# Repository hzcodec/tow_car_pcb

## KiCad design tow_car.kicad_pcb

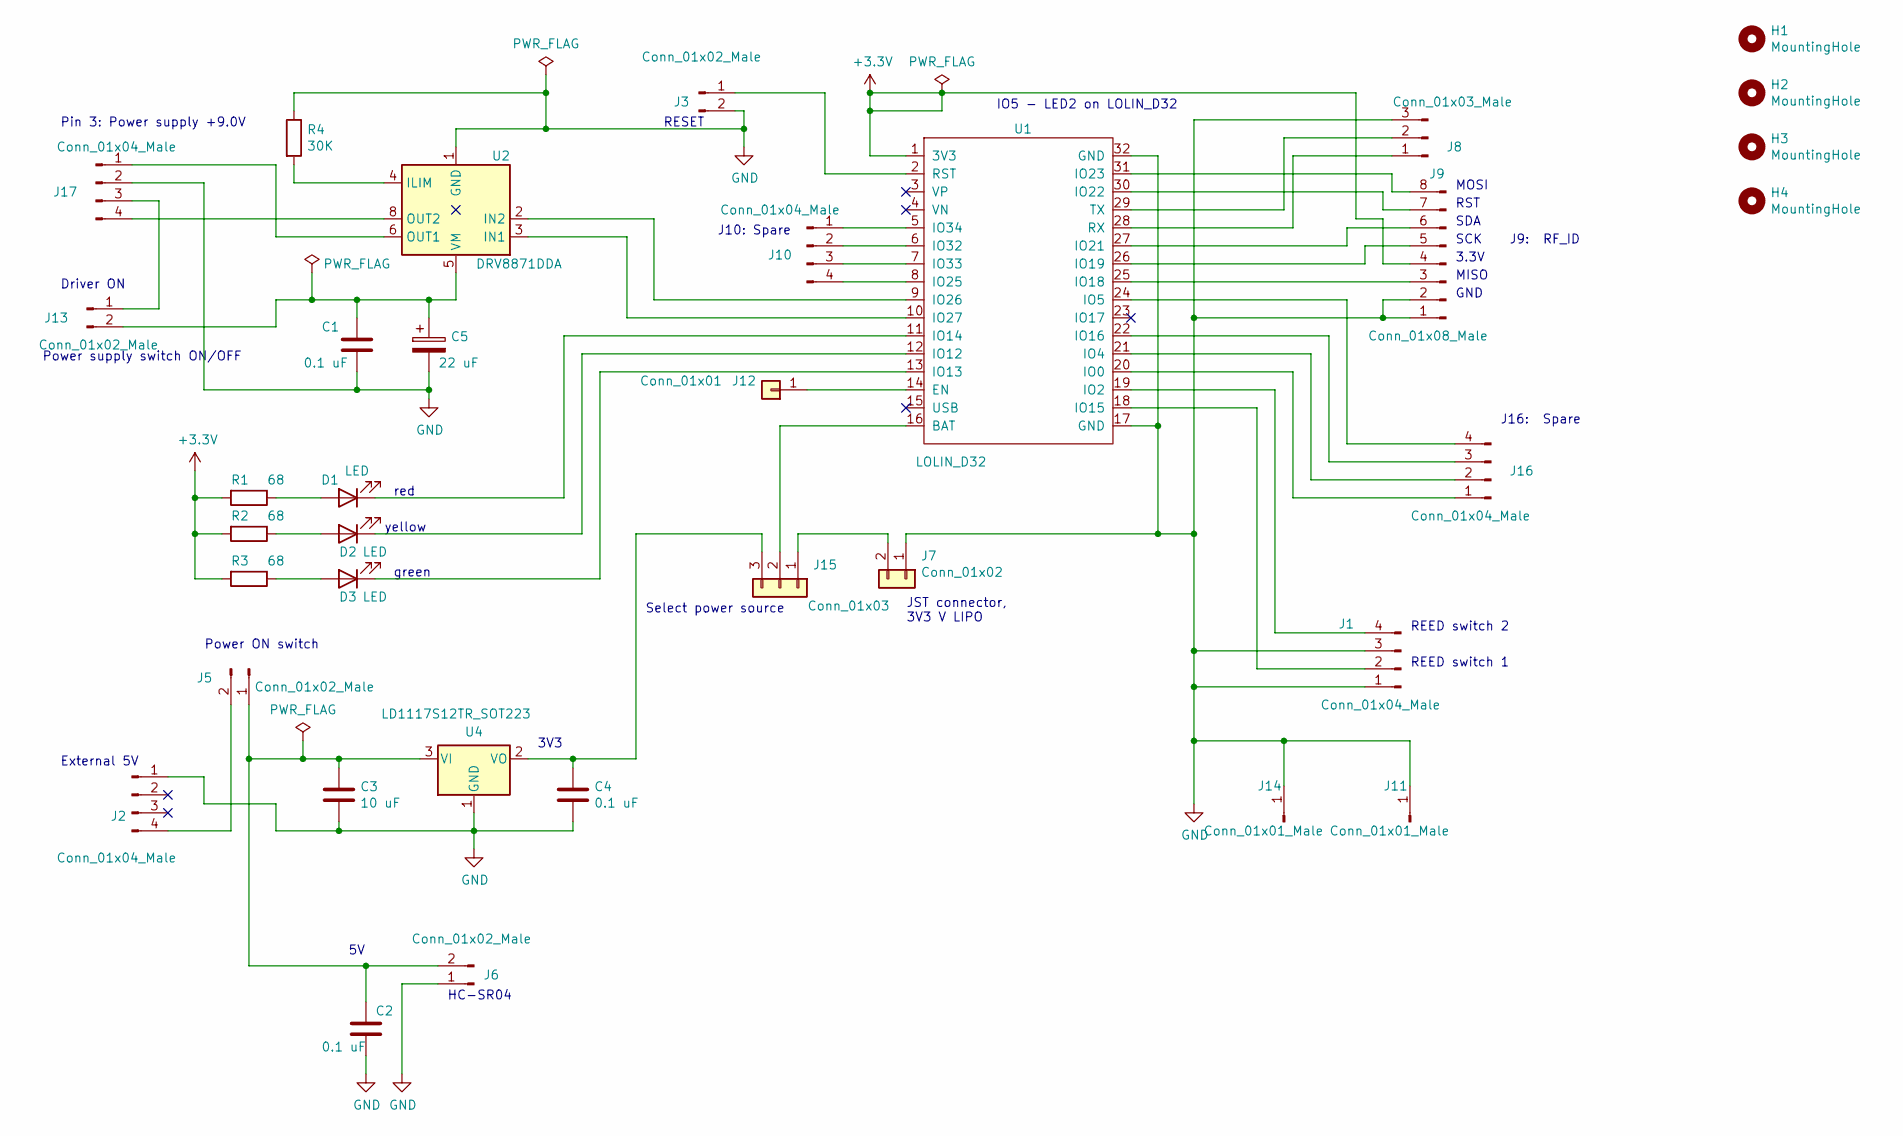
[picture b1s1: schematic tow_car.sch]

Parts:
C1, C2, C4: 0.1 uF; C_1206_3216Metric
C3: 10 uF; C_1206_3216Metric
C5: 22 uF; CP_Elec_3x5.3
D1, D2, D3: LED; LED_1206_3216Metric
H1, H2, H3, H4: MountingHole; MountingHole_3.2mm_M3
J1, J10, J16, J17: Conn_01x04_Male; Molex_Micro-Fit_3.0_43045-0412_2x02_P3.00mm_Vertical
J2: Conn_01x04_Male; USB_A_Molex_105057_Vertical
J3, J5, J6, J13: Conn_01x02_Male; PinHeader_1x02_P2.54mm_Vertical
J7: Conn_01x02; JST_PH_B2B-PH-K_1x02_P2.00mm_Vertical
J8: Conn_01x03_Male; PinHeader_1x03_P2.54mm_Vertical
J9: Conn_01x08_Male; Molex_Micro-Fit_3.0_43045-0800_2x04_P3.00mm_Horizontal
J11, J14: Conn_01x01_Male; PinHeader_1x01_P2.54mm_Vertical
J12: Conn_01x01; PinHeader_1x01_P2.54mm_Vertical
J15: Conn_01x03; PinHeader_1x03_P2.54mm_Vertical
R1, R2, R3: 68; R_1206_3216Metric
R4: 30K; R_1206_3216Metric
U1: LOLIN_D32; DIP32_W22.86
U2: DRV8871DDA; Texas_HTSOP-8-1EP_3.9x4.9mm_P1.27mm_EP2.95x4.9mm_Mask2.4x3.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
U4: LD1117S12TR_SOT223; SOT-223

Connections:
+3V3: J9.4, R1.2, R2.2, R3.2, U1.1 (3V3)
GND: C1.2, C2.2, C3.2, C4.2, C5.2, J1.1, J1.3, J2.1, J3.2, J6.1, J7.1, J8.3, J9.1, J9.2, J11.1, J14.1, J17.2, R4.1, U1.17 (GND), U1.32 (GND), U2.1 (GND), U2.7 (GND), U2.9 (GND), U4.1 (GND); also elsewhere on the board
unnamed: C1.1, C5.1, J13.2, U2.5 (VM)
unnamed: C2.1, C3.1, J5.1, J6.2, U4.3 (VI)
unnamed: C4.1, J15.3, U4.2 (VO)
unnamed: D1.1 (K), U1.11 (IO14)
unnamed: D1.2 (A), R1.1
unnamed: D2.1 (K), U1.12 (IO12)
unnamed: D2.2 (A), R2.1
unnamed: D3.1 (K), U1.13 (IO13)
unnamed: D3.2 (A), R3.1
unnamed: J1.2, U1.18 (IO15)
unnamed: J1.4, U1.19 (IO2)
unnamed: J2.4, J5.2
unnamed: J3.1, U1.2 (RST)
unnamed: J8.1, U1.28 (RX)
unnamed: J8.2, U1.29 (TX)
unnamed: J9.3, U1.25 (IO18)
unnamed: J9.5, U1.26 (IO19)
unnamed: J9.6, U1.27 (IO21)
unnamed: J9.7, U1.30 (IO22)
unnamed: J9.8, U1.31 (IO23)
unnamed: J10.1, U1.5 (IO34)
unnamed: J10.2, U1.6 (IO32)
unnamed: J10.3, U1.7 (IO33)
unnamed: J10.4, U1.8 (IO25)
unnamed: J12.1, U1.14 (EN)
unnamed: J13.1, J17.3
unnamed: J7.2, J15.1
unnamed: J15.2, U1.16 (BAT)
unnamed: J16.1, U1.20 (IO0)
unnamed: J16.2, U1.21 (IO4)
unnamed: J16.3, U1.22 (IO16)
unnamed: J16.4, U1.24 (IO5)
unnamed: J17.1, U2.6 (OUT1)
unnamed: J17.4, U2.8 (OUT2)
unnamed: R4.2, U2.4 (ILIM)
unnamed: U1.9 (IO26), U2.2 (IN2)
unnamed: U1.10 (IO27), U2.3 (IN1)

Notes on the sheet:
REED switch 1
REED switch 2
HC-SR04
J9: RF_ID
RESET
green
yellow
red
IO5 - LED2 on LOLIN_D32
J10: Spare
Power ON switch
3V3
JST connector, 3V3 V LIPO
Select power source
Driver ON
External 5V
J16: Spare
Pin 3: Power supply +9.0V
Power supply switch ON/OFF
MISO
MOSI
SCK
SDA
RST
3.3V
GND

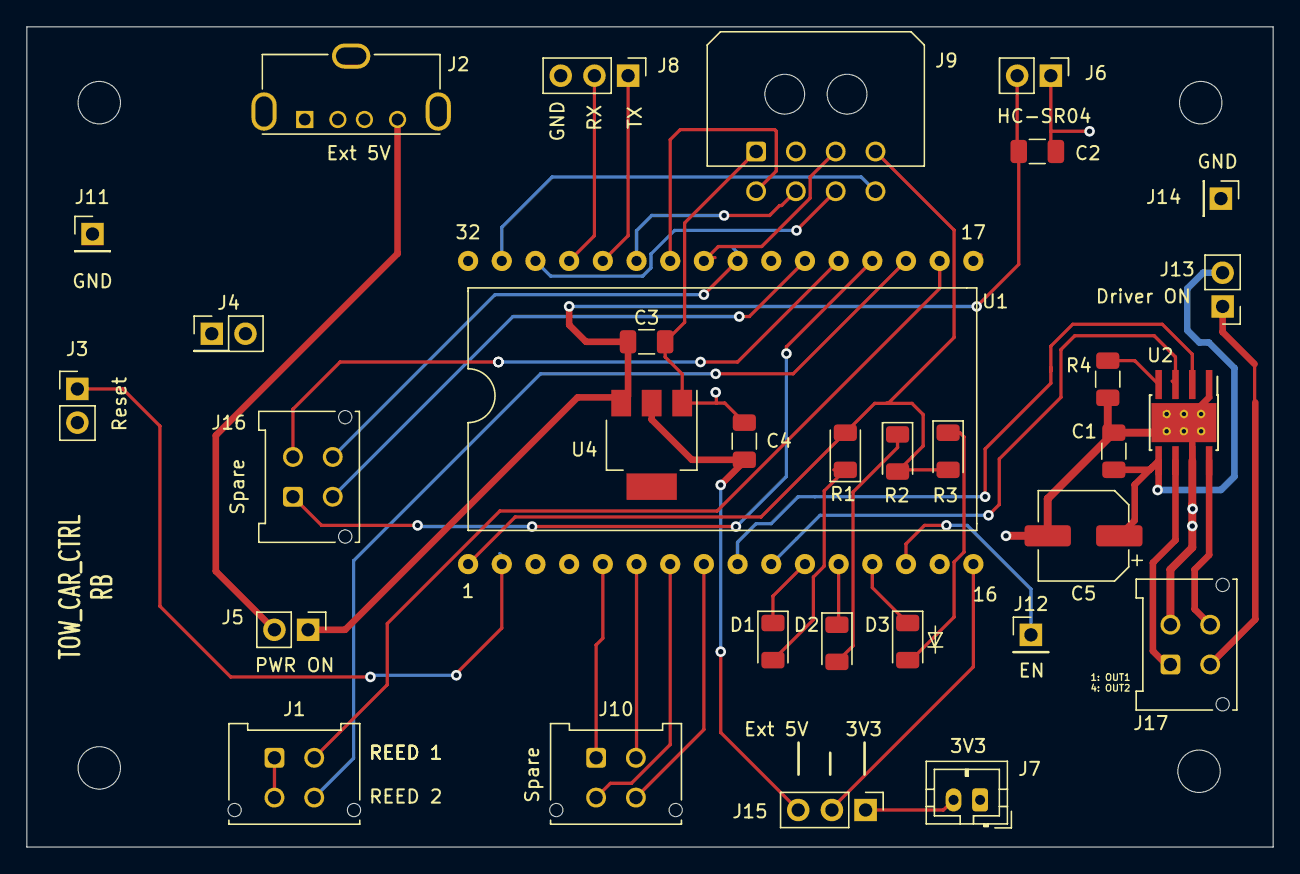
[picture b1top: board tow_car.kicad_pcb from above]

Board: 2 copper layers, 94.0 x 61.8 mm, 36 parts (0 on the bottom side), 39 nets.

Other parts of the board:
J4: Conn_01x02_Male; PinHeader_2x01_P2.54mm_Vertical

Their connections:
GND: J4.1; also elsewhere on the board

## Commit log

2020-12-28 Add gitignore
2020-12-28 First tow_car commit
2020-12-28 Update comment for J16
2021-01-02 Misc updates
2021-01-03 Update gitignore
2021-01-03 Mupp
2021-01-10 Clean up
